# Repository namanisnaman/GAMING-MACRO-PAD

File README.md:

# Gaming-Macro-Pad-
I have created a Gaming Macro Pad that you can easily build. I will provide all necessary files, including the Gerber files, CSV file, and STL files for the body. Currently, I don't have the budget to produce it right away, but I plan to start working on it within a month. After that, I will update the repository with the latest information.
# Components list below 
# Parts List

# pictures 

# I have not made it physically, so I won't be able to give bill of materials
# If you have any problem, then you can email me 
# thank you

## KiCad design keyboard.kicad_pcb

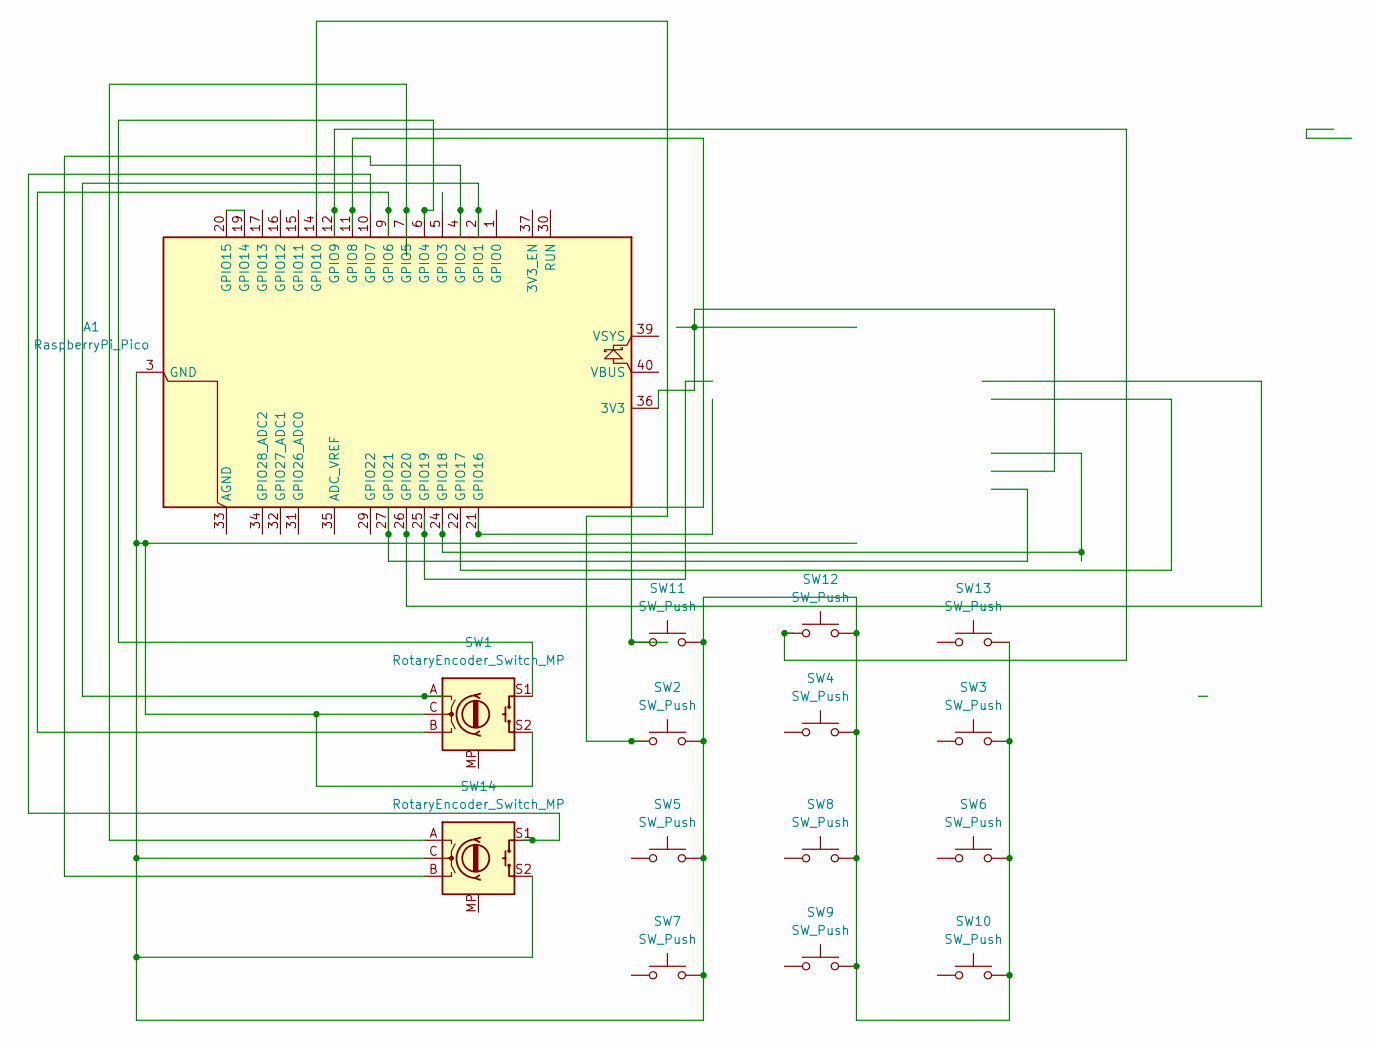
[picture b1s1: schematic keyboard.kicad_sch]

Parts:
A1: RaspberryPi_Pico; RaspberryPi_Pico_Common_Unspecified
SW1, SW14: RotaryEncoder_Switch_MP; RotaryEncoder_Alps_EC11E-Switch_Vertical_H20mm
SW2, SW3, SW4, SW5, SW6, SW7, SW8, SW9, SW10, SW11, SW12, SW13: SW_Push; SW_Cherry_MX_1.00u_PCB

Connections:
unnamed 0: A1.36 (3V3); also elsewhere on the board
unnamed: A1.2 (GPIO1), SW1.A
unnamed: A1.4 (GPIO2), SW14.B
unnamed: A1.6 (GPIO4), SW1.S1
unnamed: A1.7 (GPIO5), SW14.A
unnamed: A1.9 (GPIO6), SW1.B
unnamed: A1.10 (GPIO7), SW14.S1
unnamed: A1.11 (GPIO8), SW11.1
unnamed: A1.12 (GPIO9), SW12.1
unnamed: A1.14 (GPIO10), SW2.1
unnamed: A1.19 (GPIO14), A1.20 (GPIO15)
unnamed 11: A1.21 (GPIO16); also elsewhere on the board
unnamed 12: A1.22 (GPIO17); also elsewhere on the board
unnamed 13: A1.24 (GPIO18); also elsewhere on the board
unnamed 14: A1.25 (GPIO19); also elsewhere on the board
unnamed 15: A1.26 (GPIO20); also elsewhere on the board
unnamed 16: A1.27 (GPIO21); also elsewhere on the board
unnamed 17: A1.3 (GND), A1.8 (GND), A1.13 (GND), A1.18 (GND), A1.23 (GND), A1.28 (GND), A1.38 (GND), SW1.C, SW1.S2, SW2.2, SW3.2 (2_2), SW4.2 (2_2), SW5.2 (2_2), SW6.2 (2_2), SW7.2 (2_2), SW8.2 (2_2), SW9.2 (2_2), SW10.2 (2_2), SW11.2, SW12.2, SW13.2 (2_2), SW14.C, SW14.S2; also elsewhere on the board

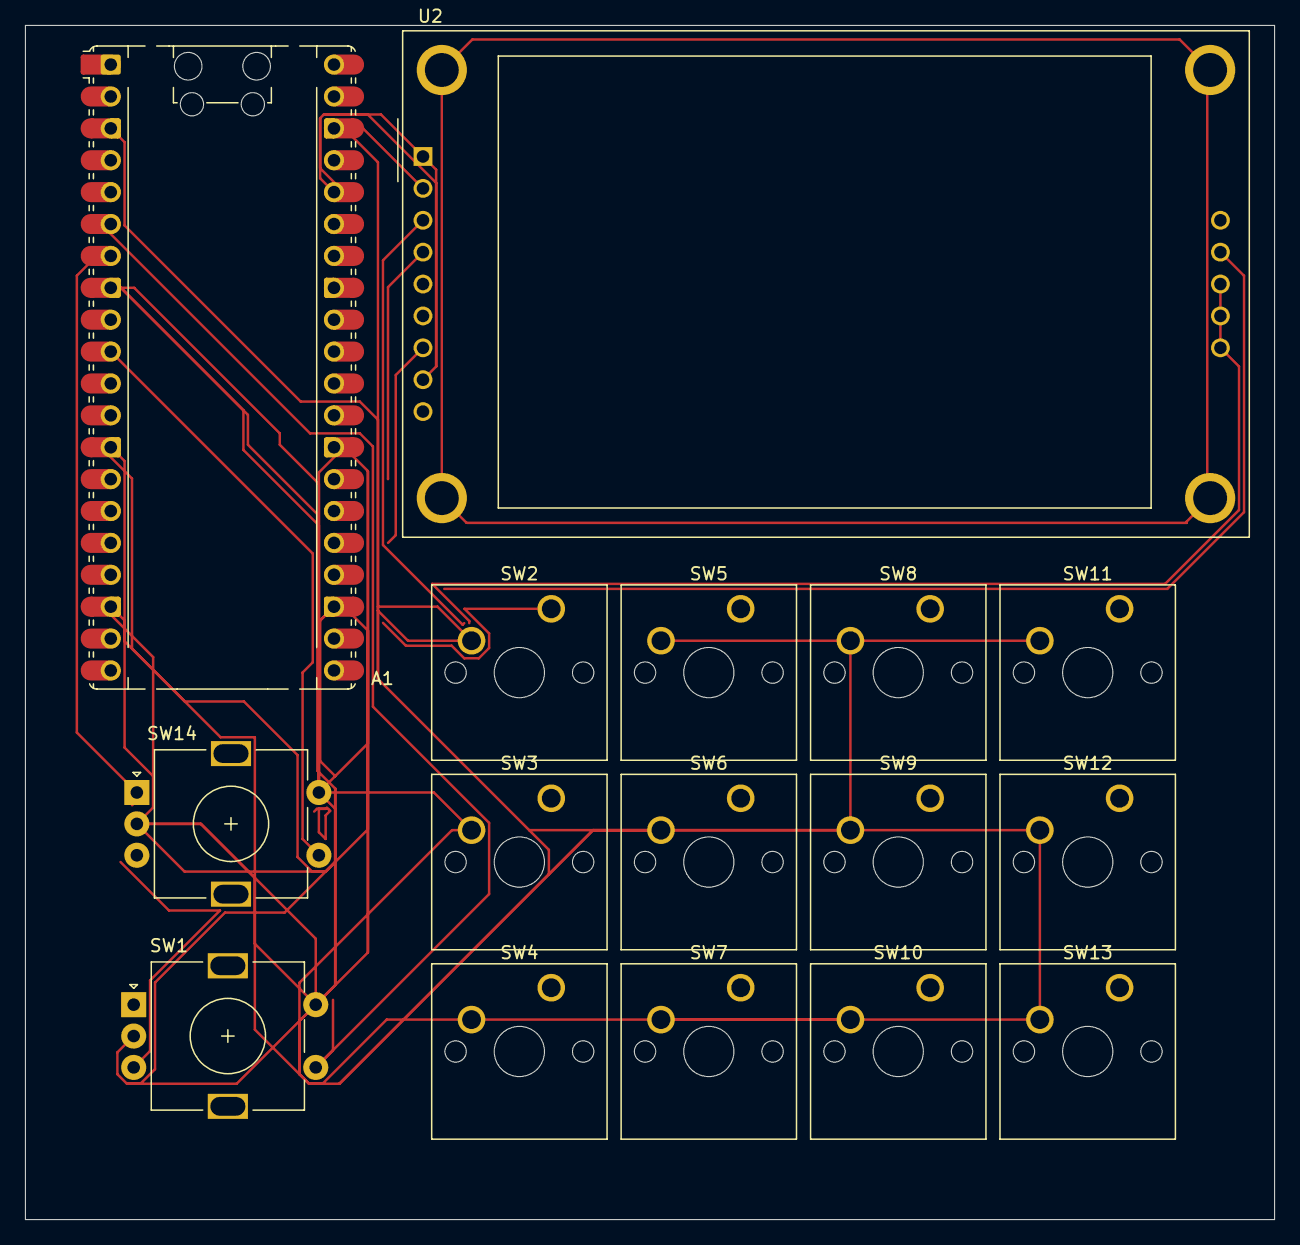
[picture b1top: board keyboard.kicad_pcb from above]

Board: 2 copper layers, 99.5 x 95.1 mm, 16 parts (0 on the bottom side), 18 nets.

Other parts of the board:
U2: CR2013-MI2120

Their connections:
unnamed 0: U2.1 (VCC), U2.8 (LED); also elsewhere on the board
unnamed 11: U2.12 (SD_MISO), U2.13 (SD_SCK), U2.14 (FLASH_CD); also elsewhere on the board
unnamed 12: U2.3 (~CS); also elsewhere on the board
unnamed 13: U2.7 (SCK); also elsewhere on the board
unnamed 14: U2.11 (SD_MOSI); also elsewhere on the board
unnamed 15: U2.5 (D/~C); also elsewhere on the board
unnamed 16: U2.4 (RESET); also elsewhere on the board
unnamed 17: U2.2 (GND); also elsewhere on the board
